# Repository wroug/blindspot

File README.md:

## What it is
BLINDSPOT is a custom project made for logging keys. It is designed to be as easy to use as possible.  It is made so one can log what's going on between their computer and keyboard, mouse or other peripherals.  
The intended purpose is to use it for either seeing whether your own computer has been used in your absence, or security testing a team on whether they identify and take action against unknown USB devices.  
> The use of it for surveilling others or gathering data without their consent is not endorsed.  

## How to assemble 
 
 1. Solder each component to it's respective pads (reference the BOM)

 2. Put the pcb in the bottom half of the case.  

3. Screw it to the case using 2x M2x4mm screws at these points.  

4. Cover it with the top half of the case, making sure the extrusions insert nicely into the slots.  

5. Secure the assembly together with a M2x8mm screw at the bottom  

**!! FLASHING INSTRUCTIONS NOT INCLUDED AS THE FIRMWARE IS NOT FINISHED.**

## Software

[ WIP ]

## Pictures

## Bom
|Reference|Qty| Value | Size | 
|--|--|--|--|
|C1, C2, C11, C15, C16, C17, C18, C19, C20, C21, C22, C23, C24|13|100nF|0603
|C3, C4, C5, C6, C12, C25, C26|7|1uF|0603
|C7, C8, C9, C10|4|27pF|0603
|C27|1|10uF|0805
|D1|1|Orange LED|0603
|D2|1|Blue LED|0603
|J2|1|480370001|-
|J3|1|292303-5|-
|R1, R2|2|33R|0603
|R3, R4|2|27R|0603
|R5, R6|2|10k|0603
|U1|1|RP2040|QFN-56_7X7
|U2|1|W25Q32JVSS|SOIC-8
|U3|1|AP2112K-3.3|SOT-23-5
|U4, U6|2|USBLC6-2SC6|SOT-23-6
|U5|1|MAX3421EETJ_|32-WFQFN-EP
|Y1, Y2|2|12MHz|5032-2

### Notes:
> The W25Q32JVSS (U2) can be substituted with any SOIC-8 flash memory chip of the same lineup (W25Q__JV) with a maximum of 128MiB space usable.

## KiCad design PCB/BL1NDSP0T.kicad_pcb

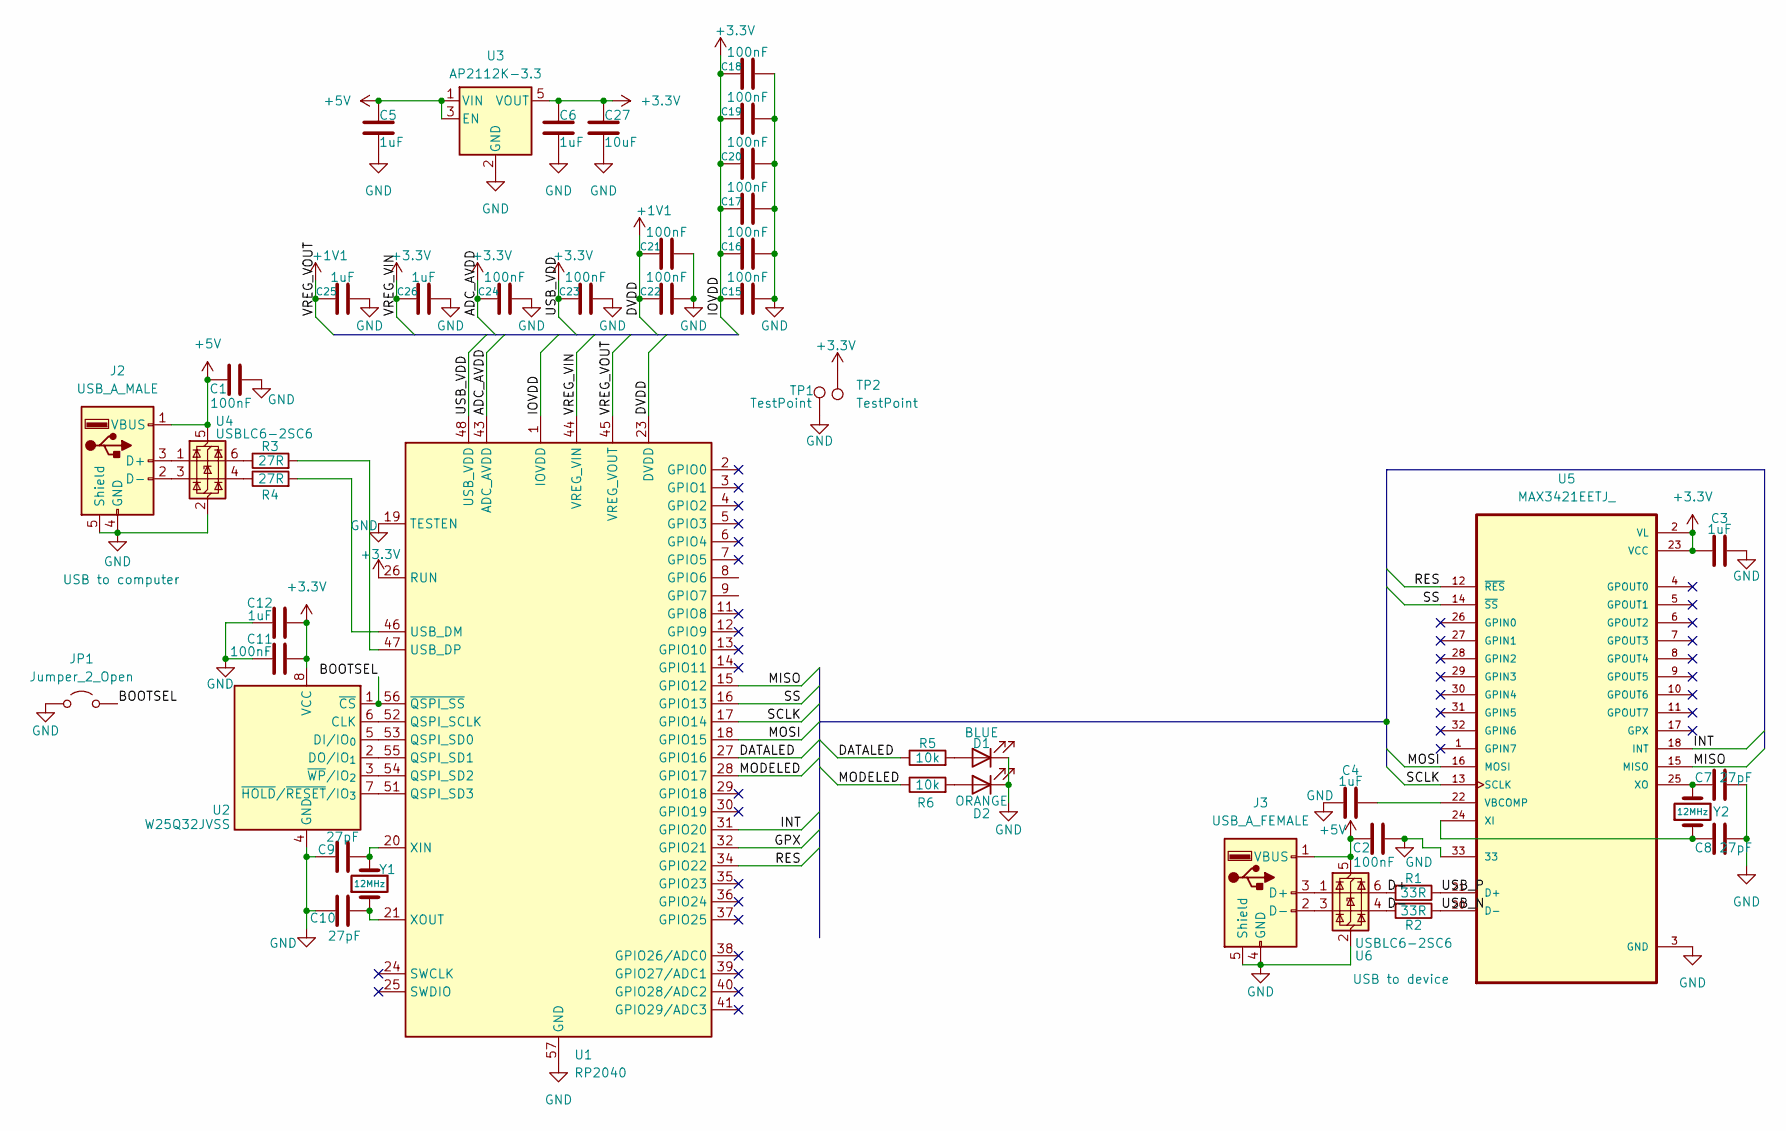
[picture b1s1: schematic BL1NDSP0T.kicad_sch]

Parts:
C1, C2, C11, C15, C16, C17, C18, C19, C20, C21, C22, C23, C24: 100nF; C_0603_1608Metric_Pad1.08x0.95mm_HandSolder
C3, C4, C5, C6, C12, C25, C26: 1uF; C_0603_1608Metric_Pad1.08x0.95mm_HandSolder
C7, C8, C9, C10: 27pF; C_0603_1608Metric_Pad1.08x0.95mm_HandSolder
C27: 10uF; C_0805_2012Metric_Pad1.18x1.45mm_HandSolder
D1: BLUE; LED_0603_1608Metric_Pad1.05x0.95mm_HandSolder
D2: ORANGE; LED_0603_1608Metric_Pad1.05x0.95mm_HandSolder
J2: USB_A_MALE; CONN_480370001_MOL
J3: USB_A_FEMALE; CONN4_292303_TEC
JP1: Jumper_2_Open; SolderJumper-2_P1.3mm_Open_Pad1.0x1.5mm
R1, R2: 33R; R_0603_1608Metric_Pad0.98x0.95mm_HandSolder
R3, R4: 27R; R_0603_1608Metric_Pad0.98x0.95mm_HandSolder
R5, R6: 10k; R_0603_1608Metric_Pad0.98x0.95mm_HandSolder
TP1, TP2: TestPoint
U1: RP2040; QFN-56-1EP_7x7mm_P0.4mm_EP3.2x3.2mm
U2: W25Q32JVSS; SOIC-8_5.3x5.3mm_P1.27mm
U3: AP2112K-3.3; SOT-23-5
U4, U6: USBLC6-2SC6; SOT-23-6
U5: MAX3421EETJ_; 21-0140L_T3255-4_MXM
Y1, Y2: 12MHz; Crystal_SMD_5032-2Pin_5.0x3.2mm_HandSoldering

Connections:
+1V1: C21.1, C22.1, C25.1, U1.23 (DVDD), U1.45 (VREG_VOUT), U1.50 (DVDD)
+3.3V: C3.1, C6.1, C11.2, C12.2, C15.1, C16.1, C17.1, C18.1, C19.1, C20.1, C23.1, C24.1, C26.1, C27.1, TP2.1, U1.1 (IOVDD), U1.10 (IOVDD), U1.22 (IOVDD), U1.26 (RUN), U1.33 (IOVDD), U1.42 (IOVDD), U1.43 (ADC_AVDD), U1.44 (VREG_VIN), U1.48 (USB_VDD), U1.49 (IOVDD), U2.8 (VCC), U3.5 (VOUT), U5.2 (VL), U5.23 (VCC)
+5V: C1.1, C2.1, C5.1, J2.1 (VBUS), J3.1 (VBUS), U3.1 (VIN), U3.3 (EN), U4.5 (VBUS), U6.5 (VBUS)
/BOOTSEL: JP1.2 (B), U1.56 (~QSPI_SS), U2.1 (~CS)
/D+: R1.2, U6.6 (I/O1)
/D-: R2.2, U6.4 (I/O2)
/DATALED: R5.1, U1.27 (GPIO16)
/GPX: U1.32 (GPIO21)
/INT: U1.31 (GPIO20), U5.18 (INT)
/MISO: U1.15 (GPIO12), U5.15 (MISO)
/MODELED: R6.1, U1.28 (GPIO17)
/MOSI: U1.18 (GPIO15), U5.16 (MOSI)
/RES: U1.34 (GPIO22), U5.12 (~RES)
/SCLK: U1.17 (GPIO14), U5.13 (SCLK)
/SS: U1.16 (GPIO13), U5.14 (~SS)
/USB_N: R2.1, U5.20 (D-)
/USB_P: R1.1, U5.21 (D+)
GND: C1.2, C2.2, C3.2, C4.1, C5.2, C6.2, C7.2, C8.2, C9.1, C10.1, C11.1, C12.1, C15.2, C16.2, C17.2, C18.2, C19.2, C20.2, C21.2, C22.2, C23.2, C24.2, C25.2, C26.2, C27.2, D1.1 (K), D2.1 (K), J2.4 (GND), J2.5 (Shield), J3.4 (GND), J3.5 (Shield), JP1.1 (A), TP1.1, U1.19 (TESTEN), U1.57 (GND), U2.4 (GND), U3.2 (GND), U4.2 (GND), U5.3 (GND), U5.19 (GND), U5.33, U6.2 (GND)
unnamed: D1.2 (A), R5.2
unnamed: D2.2 (A), R6.2
unnamed: J2.3 (D+), U4.1 (I/O1)
unnamed: J2.2 (D-), U4.3 (I/O2)
unnamed: J3.3 (D+), U6.1 (I/O1)
unnamed: J3.2 (D-), U6.3 (I/O2)
unnamed: R3.1, U4.6 (I/O1)
unnamed: R4.1, U4.4 (I/O2)
unnamed: U1.52 (QSPI_SCLK), U2.6 (CLK)
unnamed: U1.53 (QSPI_SD0), U2.5 (DI/IO_{0})
unnamed: U1.55 (QSPI_SD1), U2.2 (DO/IO_{1})
unnamed: U1.54 (QSPI_SD2), U2.3 (~WP/IO_{2})
unnamed: U1.51 (QSPI_SD3), U2.7 (~HOLD/~RESET/IO_{3})
unnamed: R4.2, U1.46 (USB_DM)
unnamed: R3.2, U1.47 (USB_DP)
unnamed: C9.2, U1.20 (XIN), Y1.2
unnamed: C10.2, U1.21 (XOUT), Y1.1
unnamed: C4.2, U5.22 (VBCOMP)
unnamed: C8.1, U5.24 (XI), Y2.1
unnamed: C7.1, U5.25 (XO), Y2.2

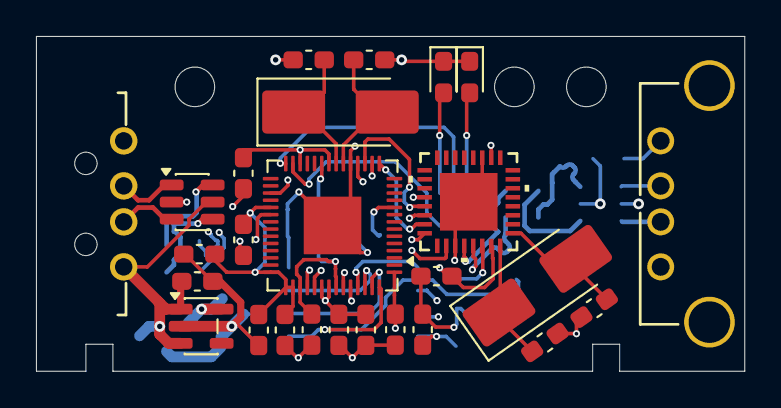
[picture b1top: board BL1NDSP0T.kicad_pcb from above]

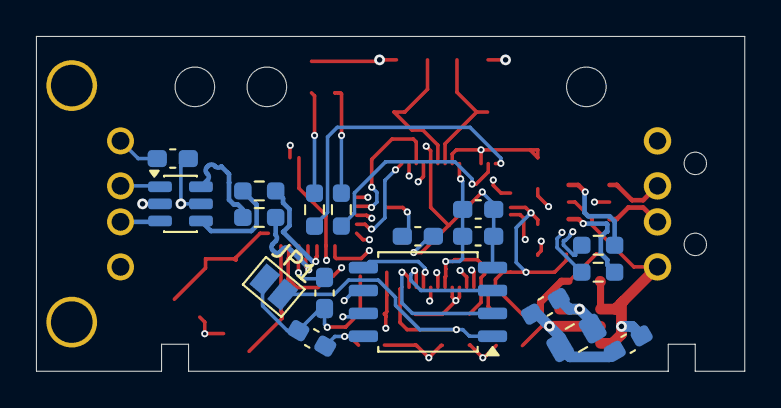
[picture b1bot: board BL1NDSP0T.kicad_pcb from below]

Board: 4 copper layers, 39.3 x 18.6 mm, 44 parts (18 on the bottom side), 37 nets.

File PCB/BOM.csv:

Reference,Qty,Value,DNP,Exclude from BOM,Exclude from Board,Footprint,Datasheet
"C1,C2,C11,C15,C16,C17,C18,C19,C20,C21,C22,C23,C24",13,100nF,,,,Capacitor_SMD:C_0603_1608Metric_Pad1.08x0.95mm_HandSolder,~
"C3,C4,C5,C6,C12,C25,C26",7,1uF,,,,Capacitor_SMD:C_0603_1608Metric_Pad1.08x0.95mm_HandSolder,~
"C7,C8,C9,C10",4,27pF,,,,Capacitor_SMD:C_0603_1608Metric_Pad1.08x0.95mm_HandSolder,~
C27,1,10uF,,,,Capacitor_SMD:C_0805_2012Metric_Pad1.18x1.45mm_HandSolder,~
D1,1,LED_BLUE,,,,LED_SMD:LED_0603_1608Metric_Pad1.05x0.95mm_HandSolder,~
D2,1,LED_ORANGE,,,,LED_SMD:LED_0603_1608Metric_Pad1.05x0.95mm_HandSolder,~
J2,1,USB_A_MALE,,,,480370001:CONN_480370001_MOL,~
J3,1,USB_A_FEMALE,,,,292303-5:CONN4_292303_TEC,~
"R1,R2",2,33R,,,,Resistor_SMD:R_0603_1608Metric_Pad0.98x0.95mm_HandSolder,~
"R3,R4",2,27R,,,,Resistor_SMD:R_0603_1608Metric_Pad0.98x0.95mm_HandSolder,~
"R5,R6",2,10k,,,,Resistor_SMD:R_0603_1608Metric_Pad0.98x0.95mm_HandSolder,~
"TP1,TP2",2,TestPoint,,,,,~
U1,1,RP2040,,,,Package_DFN_QFN:QFN-56-1EP_7x7mm_P0.4mm_EP3.2x3.2mm,https://datasheets.raspberrypi.com/rp2040/rp2040-datasheet.pdf
U2,1,W25Q32JVSS,,,,Package_SO:SOIC-8_5.3x5.3mm_P1.27mm,http://www.winbond.com/resource-files/w25q32jv%20revg%200327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
U3,1,AP2112K-3.3,,,,Package_TO_SOT_SMD:SOT-23-5,https://www.diodes.com/assets/Datasheets/AP2112.pdf
"U4,U6",2,USBLC6-2SC6,,,,Package_TO_SOT_SMD:SOT-23-6,https://www.st.com/resource/en/datasheet/usblc6-2.pdf
U5,1,MAX3421EETJ_,,,,MAX3421EETJ:21-0140L_T3255-4_MXM,
"Y1,Y2",2,12MHz,,,,Crystal:Crystal_SMD_5032-2Pin_5.0x3.2mm_HandSoldering,~
